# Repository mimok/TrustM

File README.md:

# Optiga Trust M Breakout board for RPi

Design files for the Optiga Trust M Breakout board from OTS Security.

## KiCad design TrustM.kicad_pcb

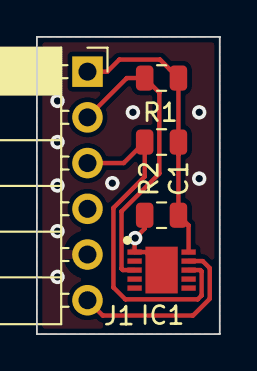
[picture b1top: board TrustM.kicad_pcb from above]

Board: 2 copper layers, 10.2 x 16.5 mm, 5 parts (0 on the bottom side), 5 nets.

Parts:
C1: 100nF; C_0805_2012Metric
IC1: SLS32AIA010MSUSON10XTMA2; SON50P300X300X60-11N-D
J1: Conn_01x06; PinSocket_1x06_P2.54mm_Horizontal
R1, R2: 4.7k; R_0805_2012Metric

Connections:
+3V3: C1.1, IC1.10, J1.1, R1.1, R2.1
/RST: IC1.9, J1.6
/SCL: IC1.8, J1.3, R2.2
/SDA: IC1.3, J1.2, R1.2
GND: C1.2, IC1.1, IC1.11, J1.5

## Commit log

2020-10-17 Add README.md
    README added with link to Tindi shop
2020-11-28 LICENSE File added
    Board design files are licensed under CC-BY 4.0
2022-03-21 Update README.md
    Remove link to Tindie because store is closed
